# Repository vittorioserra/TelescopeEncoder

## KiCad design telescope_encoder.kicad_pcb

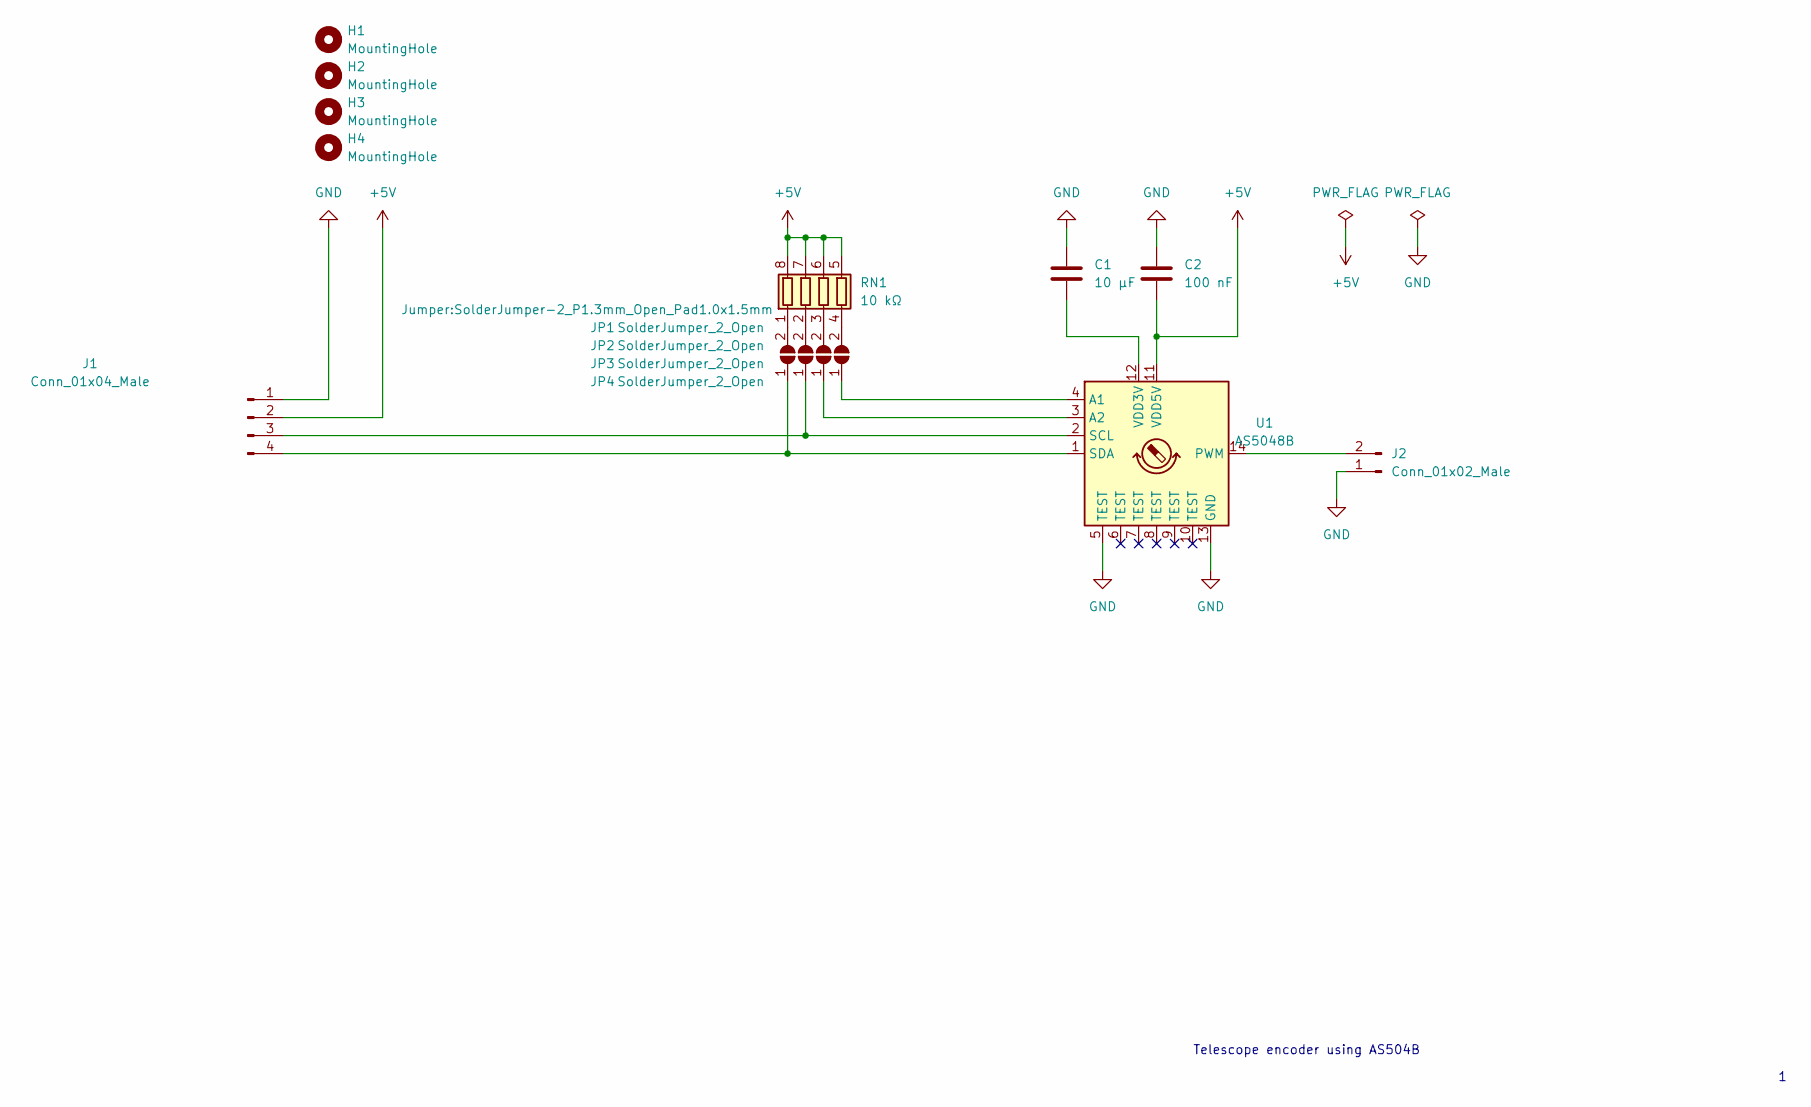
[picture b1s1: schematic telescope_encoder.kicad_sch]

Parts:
C1: 10 µF; C_1206_3216Metric_Pad1.33x1.80mm_HandSolder
C2: 100 nF; C_1206_3216Metric_Pad1.33x1.80mm_HandSolder
H1, H2, H3, H4: MountingHole; MountingHole_2.2mm_M2_DIN965
J1: Conn_01x04_Male; PinHeader_1x04_P1.27mm_Vertical_SMD_Pin1Left
J2: Conn_01x02_Male; PinHeader_1x02_P1.00mm_Vertical_SMD_Pin1Left
JP1, JP2, JP3, JP4: SolderJumper_2_Open; SolderJumper-2_P1.3mm_Open_Pad1.0x1.5mm
RN1: 10 kΩ; R_Array_Convex_4x1206
U1: AS5048B; TSSOP-14_4.4x5mm_P0.65mm

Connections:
+5V: C2.2, J1.2, RN1.5 (R4.2), RN1.6 (R3.2), RN1.7 (R2.2), RN1.8 (R1.2), U1.11 (VDD5V)
GND: C1.1, C2.1, J1.1, J2.1, U1.5 (TEST), U1.13 (GND)
unnamed: C1.2, U1.12 (VDD3V)
unnamed: J1.3, JP2.1 (A), U1.2 (SCL)
unnamed: J1.4, JP1.1 (A), U1.1 (SDA)
unnamed: J2.2, U1.14 (PWM)
unnamed: JP1.2 (B), RN1.1 (R1.1)
unnamed: JP2.2 (B), RN1.2 (R2.1)
unnamed: JP3.1 (A), U1.3 (A2)
unnamed: JP3.2 (B), RN1.3 (R3.1)
unnamed: JP4.1 (A), U1.4 (A1)
unnamed: JP4.2 (B), RN1.4 (R4.1)

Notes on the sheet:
Telescope encoder using AS504B

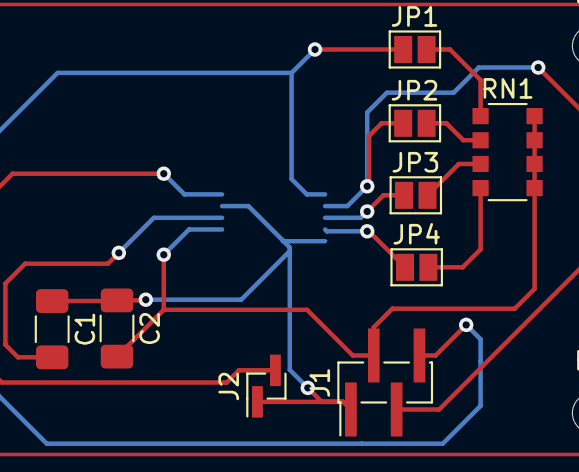
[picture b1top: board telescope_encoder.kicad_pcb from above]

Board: 2 copper layers, 14 parts (1 on the bottom side), 12 nets.

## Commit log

2022-05-11 Initial schematic and PCB commit
    Check if the size of the SMD components is fine for hand soldering
2022-05-14 Updated PCB
    The tracks need to be checked for parasitic capacitance issues
2022-05-14 Updated PCB
    Check tracks for parasitic capacitance
